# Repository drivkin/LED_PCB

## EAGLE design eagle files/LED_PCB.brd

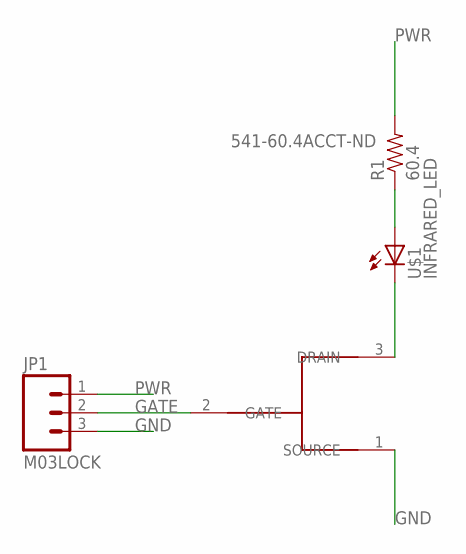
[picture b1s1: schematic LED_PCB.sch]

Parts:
JP1: M03LOCK; 1X03_LOCK
R1: 60.4; R2010; DIGIKEY_PART 541-60.4ACCT-ND
U$1: INFRARED_LED; MINI_MIDLED
U$2: N-CH_MOSFET; SOT-416

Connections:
GATE: JP1.2, U$2.2 (GATE)
GND: JP1.3, U$2.1 (SOURCE)
unnamed: R1.1, U$1.1 (A)
unnamed: U$1.2 (C), U$2.3 (DRAIN)
PWR: JP1.1, R1.2

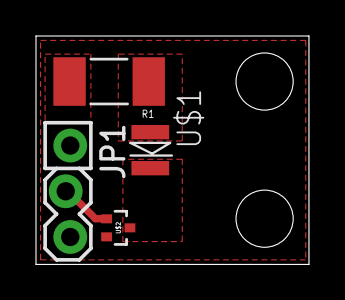
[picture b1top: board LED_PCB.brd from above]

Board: 2 copper layers, 15.2 x 12.7 mm, 4 parts (0 on the bottom side), 5 nets.

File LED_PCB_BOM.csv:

"Part";"Value";"Device";"Package";"Description";"DIGIKEY_PART";"PART_NUMBER";
"JP1";"M03LOCK";"M03LOCK";"1X03_LOCK";"Header 3";"";"";
"R1";"60.4";"RESISTOR2010";"R2010";"Resistor";"541-60.4ACCT-ND ";"";
"U$1";"INFRARED_LED";"INFRARED_LED";"MINI_MIDLED";"";"";"";
"U$2";"N-CH_MOSFET";"N-CH_MOSFET";"SOT-416";"";"2SK3019TLCT-ND";"2SK3019TL";

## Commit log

2015-05-17 :tada: Added .gitattributes & .gitignore files
2015-05-18 Made the pcb
    V1 done
